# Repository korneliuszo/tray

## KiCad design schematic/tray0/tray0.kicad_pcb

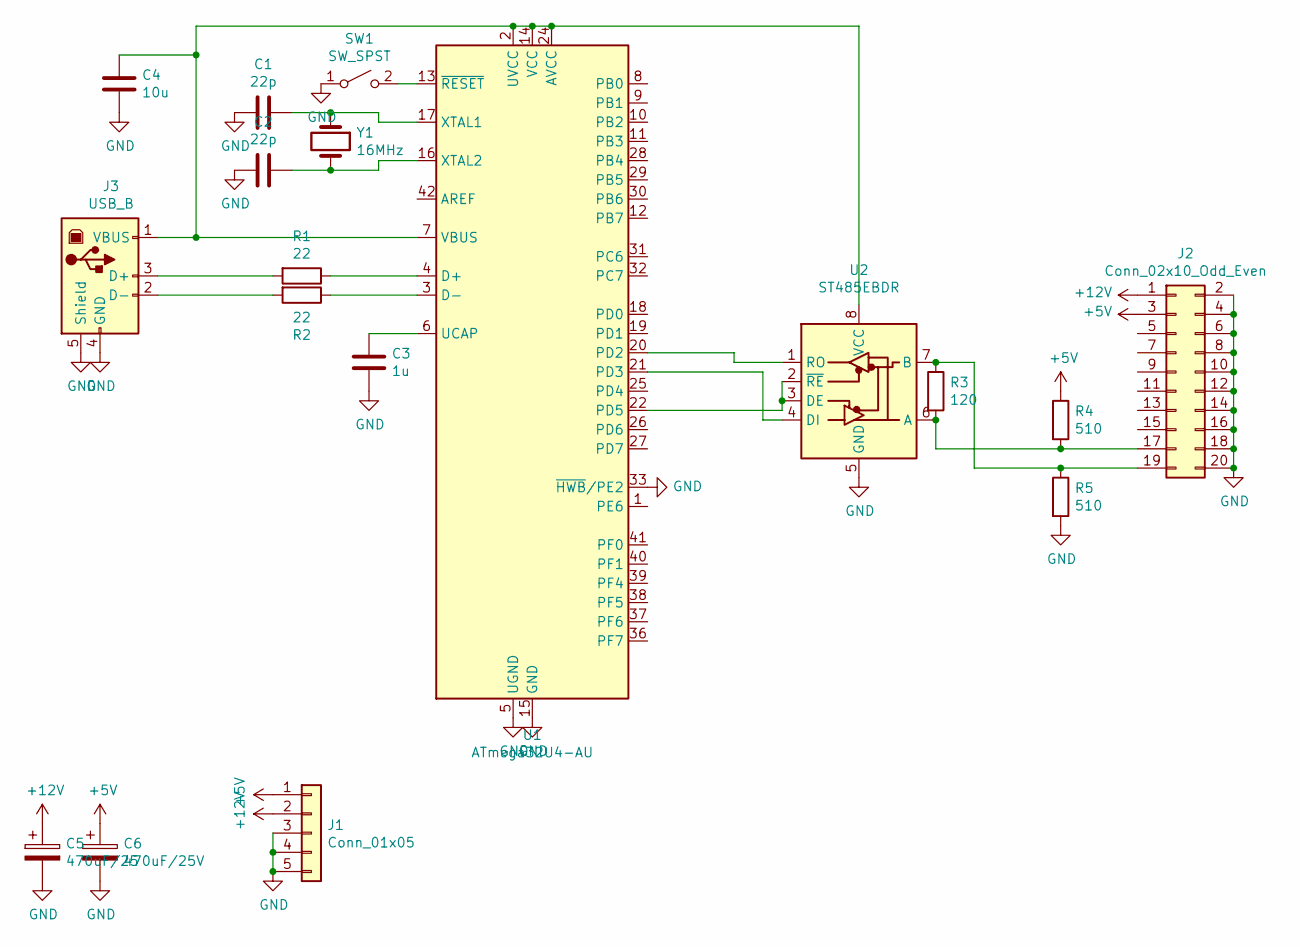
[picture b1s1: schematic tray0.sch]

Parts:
C1, C2: 22p; C_0805_2012Metric
C3: 1u; C_0805_2012Metric
C4: 10u; C_0805_2012Metric
C5: 470uF/25; CP_Radial_D8.0mm_P3.80mm
C6: 470uF/25V; CP_Radial_D8.0mm_P3.80mm
J1: Conn_01x05; PC-MDJ-402-4P
J2: Conn_02x10_Odd_Even; IDC-Header_2x10_P2.54mm_Horizontal
J3: USB_B; USB_B_OST_USB-B1HSxx_Horizontal
R1, R2: 22; R_0805_2012Metric
R3: 120; R_0805_2012Metric
R4, R5: 510; R_0805_2012Metric
SW1: SW_SPST; SW_Tactile_SKHH_Angled
U1: ATmega32U4-AU; TQFP-44_10x10mm_P0.8mm
U2: ST485EBDR; SOIC-8_3.9x4.9mm_P1.27mm
Y1: 16MHz; Crystal_SMD_HC49-SD

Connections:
+5V: C6.1, J1.1, J2.3, R4.1
+12V: C5.1, J1.2, J2.1
GND: C1.2, C2.2, C3.2, C4.2, C5.2, C6.2, J1.3, J1.4, J1.5, J2.2, J2.4, J2.6, J2.8, J2.10, J2.12, J2.14, J2.16, J2.18, J2.20, J3.4 (GND), J3.5 (Shield), R5.2, SW1.1 (A), U1.5 (UGND), U1.15 (GND), U1.23 (GND), U1.33 (~HWB~/PE2), U1.35 (GND), U1.43 (GND), U2.5 (GND)
unnamed: C1.1, U1.17 (XTAL1), Y1.1
unnamed: C2.1, U1.16 (XTAL2), Y1.2
unnamed: C3.1, U1.6 (UCAP)
unnamed: C4.1, J3.1 (VBUS), U1.2 (UVCC), U1.7 (VBUS), U1.14 (VCC), U1.24 (AVCC), U1.34 (VCC), U1.44 (AVCC), U2.8 (VCC)
unnamed: J2.17, R3.2, R4.2, U2.6 (A)
unnamed: J2.19, R3.1, R5.1, U2.7 (B)
unnamed: J3.2 (D-), R2.2
unnamed: J3.3 (D+), R1.2
unnamed: R1.1, U1.4 (D+)
unnamed: R2.1, U1.3 (D-)
unnamed: SW1.2 (B), U1.13 (~RESET)
unnamed: U1.20 (PD2), U2.1 (RO)
unnamed: U1.21 (PD3), U2.4 (DI)
unnamed: U1.22 (PD5), U2.2 (~RE), U2.3 (DE)

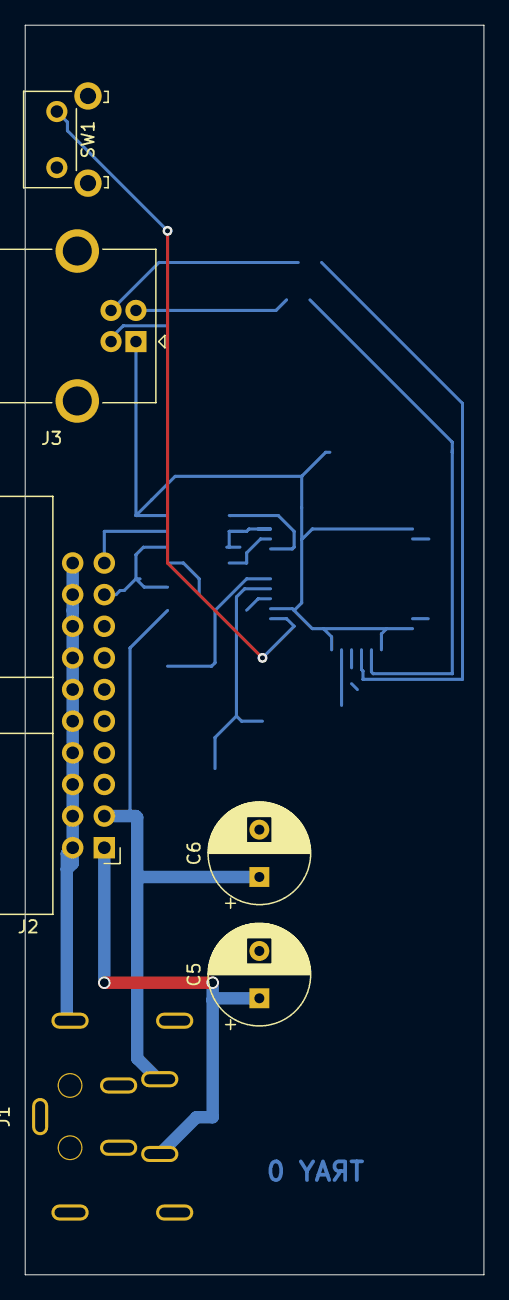
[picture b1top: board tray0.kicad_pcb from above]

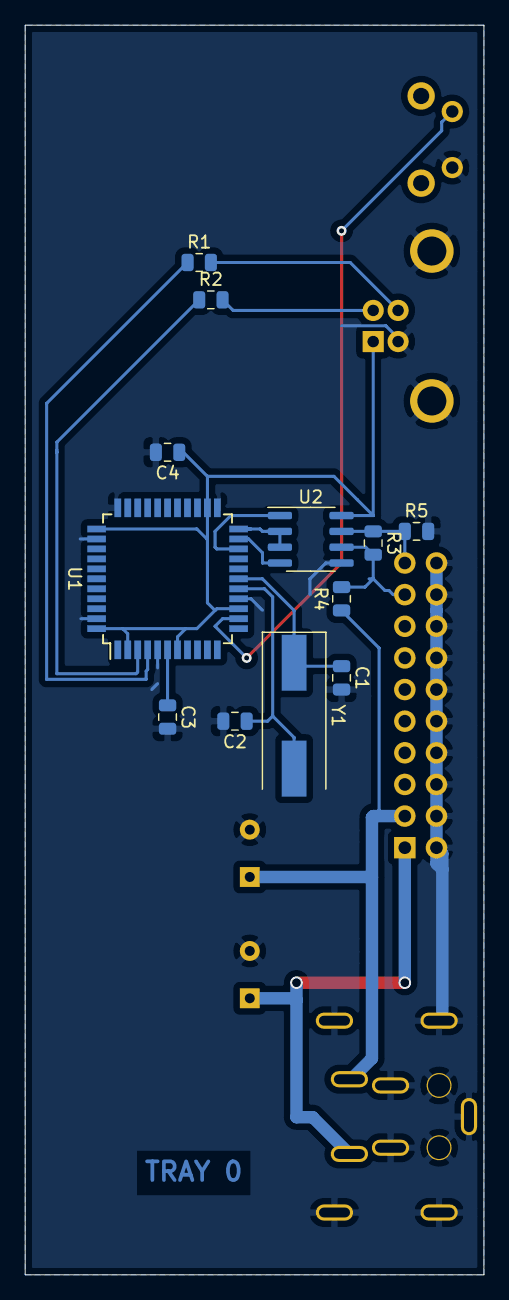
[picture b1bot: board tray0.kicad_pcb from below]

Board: 2 copper layers, 36.8 x 100.3 mm, 18 parts (12 on the bottom side), 17 nets.

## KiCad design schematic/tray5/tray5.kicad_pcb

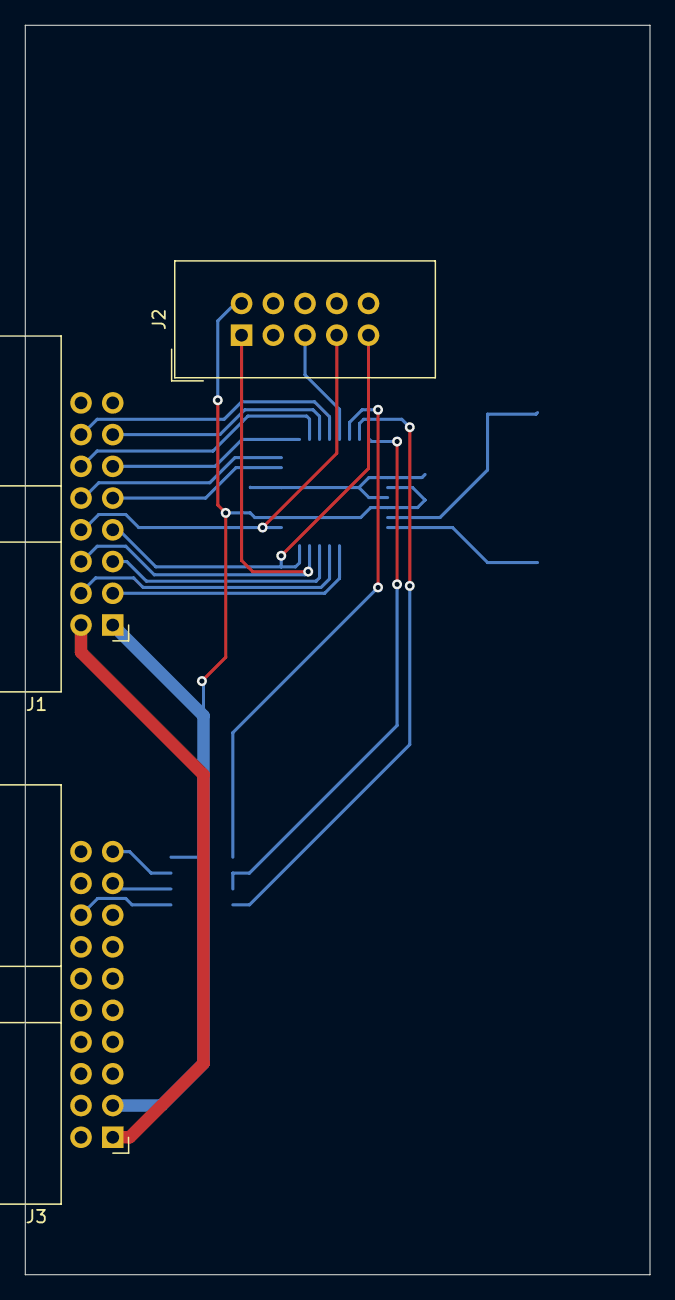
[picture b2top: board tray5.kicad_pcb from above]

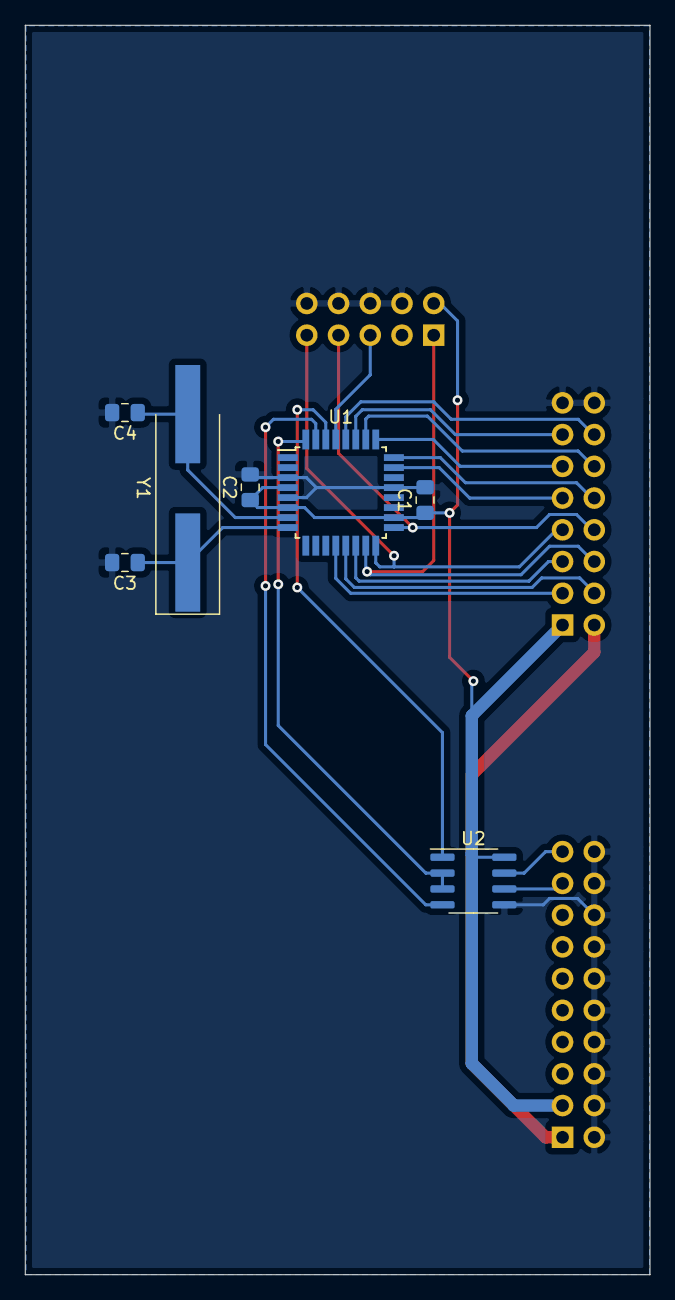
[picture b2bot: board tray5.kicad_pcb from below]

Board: 2 copper layers, 50.0 x 100.0 mm, 10 parts (7 on the bottom side), 23 nets.

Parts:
C1, C2: 100nF; C_0805_2012Metric_Pad1.15x1.40mm_HandSolder
C3, C4: 27p; C_0805_2012Metric_Pad1.15x1.40mm_HandSolder
J1: Conn_02x08_Odd_Even; IDC-Header_2x08_P2.54mm_Horizontal
J2: AVR-ISP-10; IDC-Header_2x05_P2.54mm_Vertical
J3: Conn_02x10_Odd_Even; IDC-Header_2x10_P2.54mm_Horizontal
U1: ATmega328P-AU; TQFP-32_7x7mm_P0.8mm
U2: ST485EBDR; SOIC-8_3.9x4.9mm_P1.27mm
Y1: 16MHz; Crystal_SMD_HC49-SD_HandSoldering

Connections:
GND: C1.2, C2.2, C3.2, C4.2, J1.15, J1.16, J2.4, J2.6, J2.8, J2.10, J3.2, J3.4, J3.6, J3.8, J3.10, J3.12, J3.14, J3.16, J3.18, J3.20, U1.3, U1.5, U1.21, U2.5
unnamed: C3.1, U1.8, Y1.1
unnamed: C4.1, U1.7, Y1.2
unnamed: J1.2, J3.1
unnamed: J2.5, U1.29
unnamed: J3.17, U2.6
unnamed: J3.19, U2.7
unnamed: U1.30, U2.1
unnamed: U1.31, U2.4
unnamed: U1.32, U2.2, U2.3
PB0: J1.3, U1.12
PB1: J1.4, U1.13
PB2: J1.5, U1.14
PB3: J1.6, J2.1, U1.15
PB4: J1.7, J2.9, U1.16
PB5: J1.8, J2.7, U1.17
PC0: J1.9, U1.23
PC1: J1.10, U1.24
PC2: J1.11, U1.25
PC3: J1.12, U1.26
PC4: J1.13, U1.27
PC5: J1.14, U1.28
VCC: C1.1, C2.1, J1.1, J2.2, J3.3, U1.4, U1.6, U1.18, U2.8

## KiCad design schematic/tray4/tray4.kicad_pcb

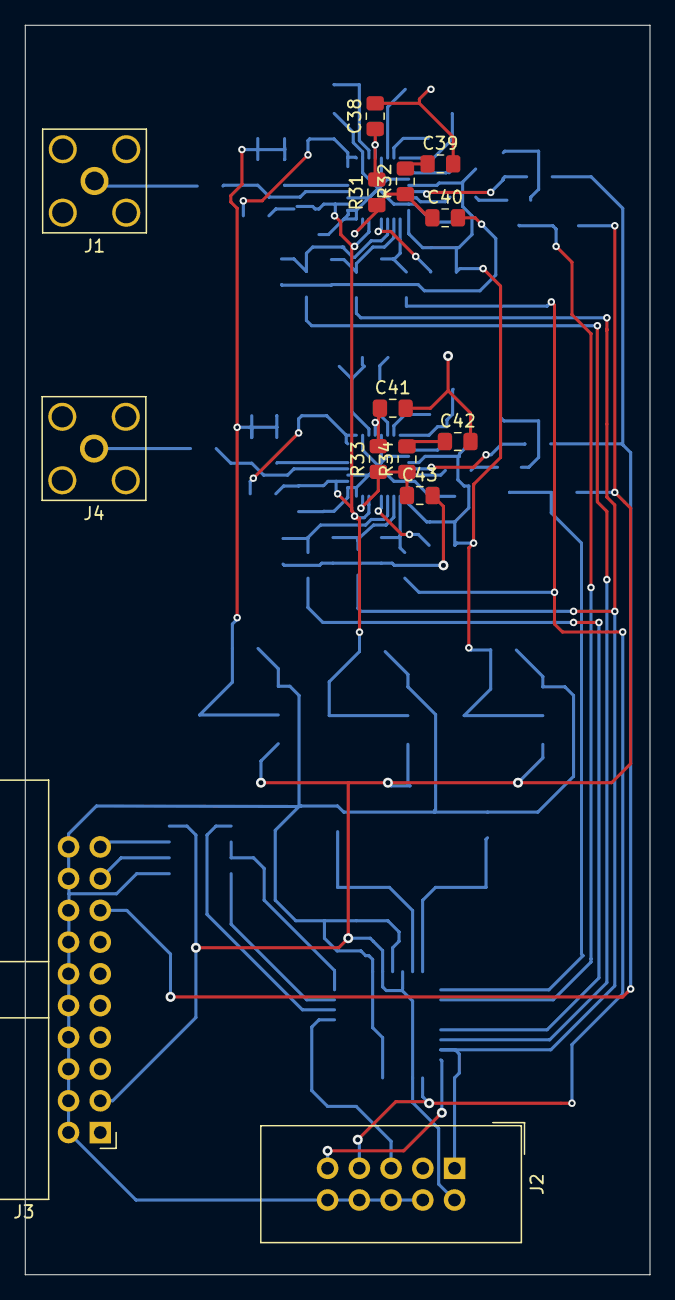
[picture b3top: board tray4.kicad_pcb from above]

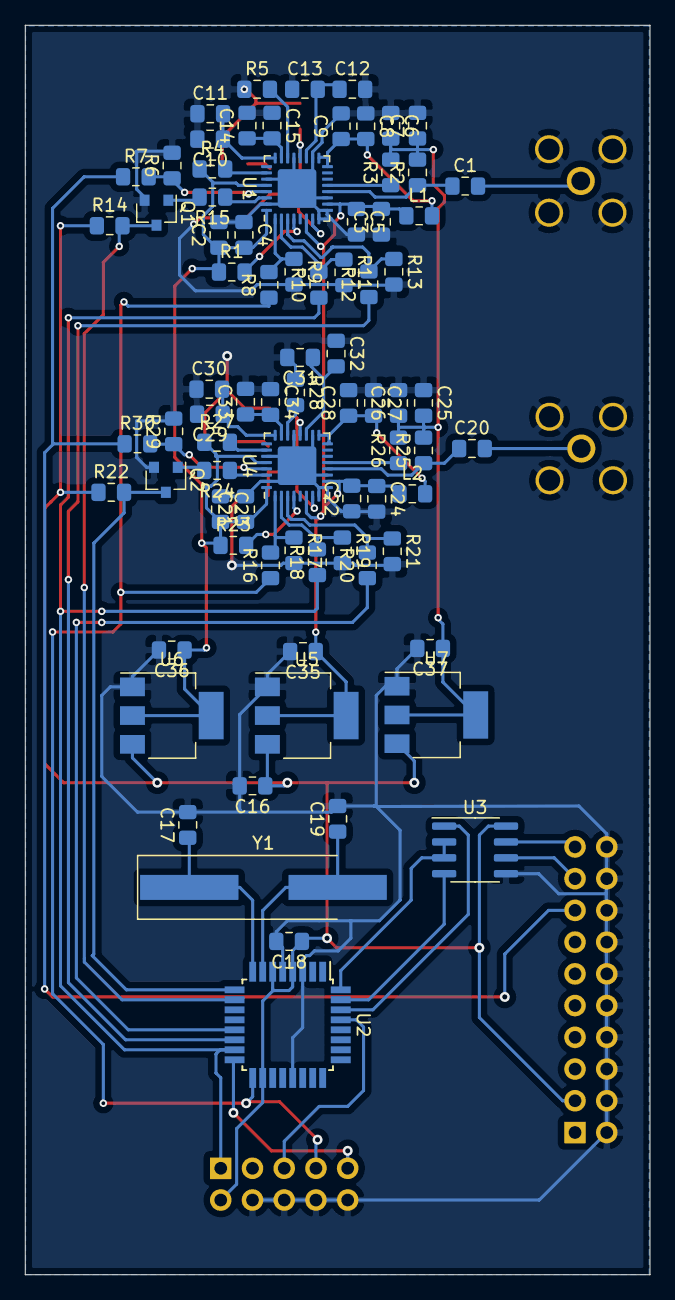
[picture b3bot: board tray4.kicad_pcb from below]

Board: 2 copper layers, 50.0 x 100.0 mm, 93 parts (79 on the bottom side), 59 nets.

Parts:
C1, C20: 100p; C_0805_2012Metric_Pad1.15x1.40mm_HandSolder
C2, C5, C7, C9, C10, C12, C14, C21, C24, C26, C28, C29, C31, C33: 10p; C_0805_2012Metric_Pad1.15x1.40mm_HandSolder
C3, C4, C6, C8, C11, C13, C15, C22, C23, C25, C27, C30, C32, C34, C35, C36, C37: 100n; C_0805_2012Metric_Pad1.15x1.40mm_HandSolder
C16, C18: 100nF; C_0805_2012Metric_Pad1.15x1.40mm_HandSolder
C17, C19: 27p; C_0805_2012Metric_Pad1.15x1.40mm_HandSolder
C38, C41: 10n; C_0805_2012Metric_Pad1.15x1.40mm_HandSolder
C39, C42: 330n; C_0805_2012Metric_Pad1.15x1.40mm_HandSolder
C40, C43: 22n; C_0805_2012Metric_Pad1.15x1.40mm_HandSolder
J1, J4: Conn_Coaxial; SMA_Amphenol_132203-12_Horizontal
J2: AVR-ISP-10; IDC-Header_2x05_P2.54mm_Vertical
J3: Conn_02x10_Odd_Even; IDC-Header_2x10_P2.54mm_Horizontal
L1, L2: 47n; L_0805_2012Metric_Pad1.15x1.40mm_HandSolder
Q1, Q2: BC847; SOT-23
R1, R4, R23, R27: 10k; R_0805_2012Metric_Pad1.15x1.40mm_HandSolder
R2, R3, R25, R26: 50; R_0805_2012Metric_Pad1.15x1.40mm_HandSolder
R5, R28: 4k7; R_0805_2012Metric_Pad1.15x1.40mm_HandSolder
R6, R9, R11, R13, R17, R19, R21, R29: 3k3; R_0805_2012Metric_Pad1.15x1.40mm_HandSolder
R7, R30: 1k8; R_0805_2012Metric_Pad1.15x1.40mm_HandSolder
R8, R10, R12, R16, R18, R20: 2k2; R_0805_2012Metric_Pad1.15x1.40mm_HandSolder
R14, R15, R22, R24: 1k; R_0805_2012Metric_Pad1.15x1.40mm_HandSolder
R31, R33: 180; R_0805_2012Metric_Pad1.15x1.40mm_HandSolder
R32, R34: 82; R_0805_2012Metric_Pad1.15x1.40mm_HandSolder
U1, U4: ADF4351; QFN-32-1EP_5x5mm_P0.5mm_EP3.1x3.1mm
U2: ATmega328P-AU; TQFP-32_7x7mm_P0.8mm
U3: ST485EBDR; SOIC-8_3.9x4.9mm_P1.27mm
U5, U6, U7: AMS1117-3.3; SOT-223-3_TabPin2
Y1: 16MHz; Crystal_SMD_HC49-SD_HandSoldering

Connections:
10MHz: J3.15, R7.1, R30.1
+3.3VA: C3.2, C5.1, C22.2, C24.1, C35.1, L1.1, L2.1, U1.6, U1.10, U4.6, U4.10, U5.2
+3.3VP: C6.2, C7.1, C25.2, C26.1, C37.1, R2.2, R3.2, R25.2, R26.2, U7.2
+3V3: C2.1, C4.2, C21.1, C23.2, C36.1, R1.1, R4.1, R23.1, R27.1, U1.28, U1.32, U4.28, U4.32, U6.2
CP0: C40.1, R31.1, R32.1, U1.7
CP1: C43.1, R33.1, R34.1, U4.7
GND: C2.2, C3.1, C4.1, C5.2, C6.1, C7.2, C8.1, C9.2, C10.2, C11.1, C12.2, C13.1, C14.2, C15.1, C16.2, C17.2, C18.2, C19.2, C21.2, C22.1, C23.1, C24.2, C25.1, C26.2, C27.1, C28.2, C29.2, C30.1, C31.2, C32.1, C33.2, C34.1, C35.2, C36.2, C37.2, C38.2, C39.2, C40.2, C41.2, C42.2, C43.2, J1.2, J2.4, J2.6, J2.8, J2.10, J3.2, J3.4, J3.6, J3.8, J3.10, J3.12, J3.14, J3.16, J3.18, J3.20, J4.2, Q1.2, Q2.2, R5.1, R6.2, R9.2, R11.2, R13.2, R17.2, R19.2, R21.2, R28.1, R29.2, U1.8, U1.9, U1.11, U1.18, U1.21, U1.27, U1.31, U1.33, U2.3, U2.5, U2.21, U3.5, U4.8, U4.9, U4.11, U4.18, U4.21, U4.27, U4.31, U4.33, U5.1, U6.1, U7.1
LE0: R12.1, U2.14
LE1: R20.1, U2.13
MOSI: J2.1, R10.1, R18.1, U2.15
MUXOUT0: Q1.3, R14.2, U2.10
MUXOUT1: Q2.3, R22.2, U2.9
unnamed: C1.1, R2.1, U1.12
unnamed: C1.2, J1.1
unnamed: C8.2, C9.1, L1.2, U1.16, U1.17
unnamed: C10.1, C11.2, U1.24
unnamed: C12.1, C13.2, U1.19
unnamed: C14.1, C15.2, U1.23
unnamed: C17.1, U2.8, Y1.1
unnamed: C19.1, U2.7, Y1.2
unnamed: C20.1, R25.1, U4.12
unnamed: C20.2, J4.1
unnamed: C27.2, C28.1, L2.2, U4.16, U4.17
unnamed: C29.1, C30.2, U4.24
unnamed: C31.1, C32.2, U4.19
unnamed: C33.1, C34.2, U4.23
unnamed: C38.1, R31.2, U1.20
unnamed: C39.1, R32.2
unnamed: C41.1, R33.2, U4.20
unnamed: C42.1, R34.2
unnamed: J2.5, U2.29
unnamed: J2.9, U2.16
unnamed: J3.17, U3.6
unnamed: J3.19, U3.7
unnamed: Q1.1, R15.2
unnamed: Q2.1, R24.2
unnamed: R1.2, U1.4
unnamed: R3.1, U1.13
unnamed: R4.2, U1.26
unnamed: R5.2, U1.22
unnamed: R6.1, R7.2, U1.29
unnamed: R8.2, R9.1, U1.1
unnamed: R10.2, R11.1, U1.2
unnamed: R12.2, R13.1, U1.3
unnamed: R15.1, U1.30
unnamed: R16.2, R17.1, U4.1
unnamed: R18.2, R19.1, U4.2
unnamed: R20.2, R21.1, U4.3
unnamed: R23.2, U4.4
unnamed: R24.1, U4.30
unnamed: R26.1, U4.13
unnamed: R27.2, U4.26
unnamed: R28.2, U4.22
unnamed: R29.1, R30.2, U4.29
unnamed: U2.30, U3.1
unnamed: U2.31, U3.4
unnamed: U2.32, U3.2, U3.3
SCK: J2.7, R8.1, R16.1, U2.17
VCC: C16.1, C18.1, J2.2, J3.3, R14.1, R22.1, U2.4, U2.6, U2.18, U3.8, U5.3, U6.3, U7.3

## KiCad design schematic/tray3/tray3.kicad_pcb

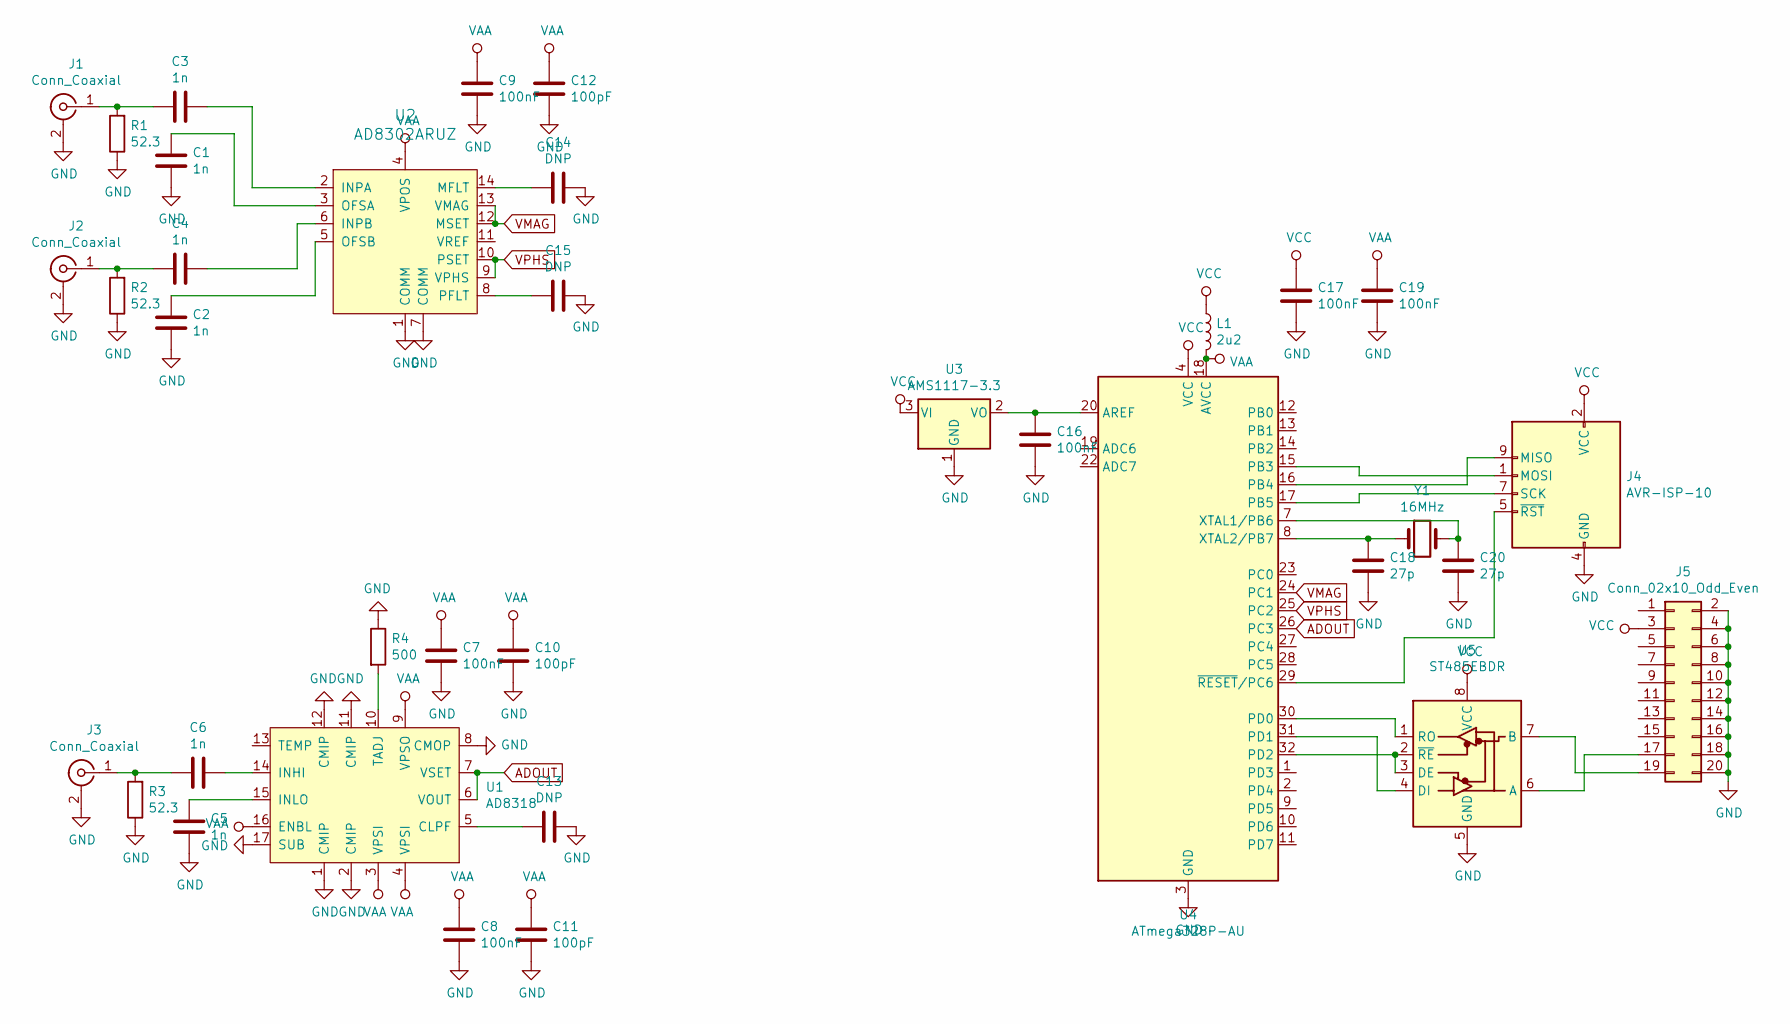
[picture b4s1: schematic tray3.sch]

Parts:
C1, C2, C3, C4, C5, C6: 1n; C_0805_2012Metric_Pad1.15x1.40mm_HandSolder
C7, C8, C9, C16, C17, C19: 100nF; C_0805_2012Metric_Pad1.15x1.40mm_HandSolder
C10, C11, C12: 100pF; C_0805_2012Metric_Pad1.15x1.40mm_HandSolder
C13, C14, C15: DNP; C_0805_2012Metric_Pad1.15x1.40mm_HandSolder
C18, C20: 27p; C_0805_2012Metric_Pad1.15x1.40mm_HandSolder
J1, J2, J3: Conn_Coaxial; SMA_Molex_73251-2200_Horizontal
J4: AVR-ISP-10; IDC-Header_2x05_P2.54mm_Vertical
J5: Conn_02x10_Odd_Even; IDC-Header_2x10_P2.54mm_Horizontal
L1: 2u2; L_1210_3225Metric_Pad1.42x2.65mm_HandSolder
R1, R2, R3: 52.3; R_1206_3216Metric_Pad1.42x1.75mm_HandSolder
R4: 500; R_0805_2012Metric_Pad1.15x1.40mm_HandSolder
U1: AD8318; QFN-16-1EP_4x4mm_P0.65mm_EP2.5x2.5mm
U2: AD8302ARUZ; TSSOP-14_4.4x5mm_P0.65mm; MPN AD8302ARUZ; Digi-Key_PN AD8302ARUZ-ND
U3: AMS1117-3.3; SOT-223-3_TabPin2
U4: ATmega328P-AU; TQFP-32_7x7mm_P0.8mm
U5: ST485EBDR; SOIC-8_3.9x4.9mm_P1.27mm
Y1: 16MHz; Crystal_SMD_HC49-SD_HandSoldering

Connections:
ADOUT: U1.6 (VOUT), U1.7 (VSET), U4.26 (PC3)
GND: C1.2, C2.2, C5.2, C7.2, C8.2, C9.2, C10.2, C11.2, C12.2, C13.1, C14.1, C15.1, C16.2, C17.2, C18.2, C19.2, C20.2, J1.2 (Ext), J2.2 (Ext), J3.2 (Ext), J4.4 (GND), J4.6 (GND), J4.8 (GND), J4.10 (GND), J5.2, J5.4, J5.6, J5.8, J5.10, J5.12, J5.14, J5.16, J5.18, J5.20, R1.1, R2.1, R3.1, R4.1, U1.1 (CMIP), U1.2 (CMIP), U1.8 (CMOP), U1.11 (CMIP), U1.12 (CMIP), U1.17 (SUB), U2.1 (COMM), U2.7 (COMM), U3.1 (GND), U4.3 (GND), U4.5 (GND), U4.21 (GND), U5.5 (GND)
unnamed: C1.1, U2.3 (OFSA)
unnamed: C2.1, U2.5 (OFSB)
unnamed: C3.1, U2.2 (INPA)
unnamed: C3.2, J1.1 (In), R1.2
unnamed: C4.1, U2.6 (INPB)
unnamed: C4.2, J2.1 (In), R2.2
unnamed: C5.1, U1.15 (INLO)
unnamed: C6.1, U1.14 (INHI)
unnamed: C6.2, J3.1 (In), R3.2
unnamed: C13.2, U1.5 (CLPF)
unnamed: C14.2, U2.14 (MFLT)
unnamed: C15.2, U2.8 (PFLT)
unnamed: C16.1, U3.2 (VO), U4.20 (AREF)
unnamed: C18.1, U4.8 (XTAL2/PB7), Y1.1
unnamed: C20.1, U4.7 (XTAL1/PB6), Y1.2
unnamed: J4.1 (MOSI), U4.15 (PB3)
unnamed: J4.5 (~RST), U4.29 (~RESET~/PC6)
unnamed: J4.7 (SCK), U4.17 (PB5)
unnamed: J4.9 (MISO), U4.16 (PB4)
unnamed: J5.17, U5.6 (A)
unnamed: J5.19, U5.7 (B)
unnamed: R4.2, U1.10 (TADJ)
unnamed: U4.30 (PD0), U5.1 (RO)
unnamed: U4.31 (PD1), U5.4 (DI)
unnamed: U4.32 (PD2), U5.2 (~RE), U5.3 (DE)
VAA: C7.1, C8.1, C9.1, C10.1, C11.1, C12.1, C19.1, L1.2, U1.3 (VPSI), U1.4 (VPSI), U1.9 (VPSO), U1.16 (ENBL), U2.4 (VPOS), U4.18 (AVCC)
VCC: C17.1, J4.2 (VCC), J5.3, L1.1, U3.3 (VI), U4.4 (VCC), U4.6 (VCC), U5.8 (VCC)
VMAG: U2.12 (MSET), U2.13 (VMAG), U4.24 (PC1)
VPHS: U2.9 (VPHS), U2.10 (PSET), U4.25 (PC2)

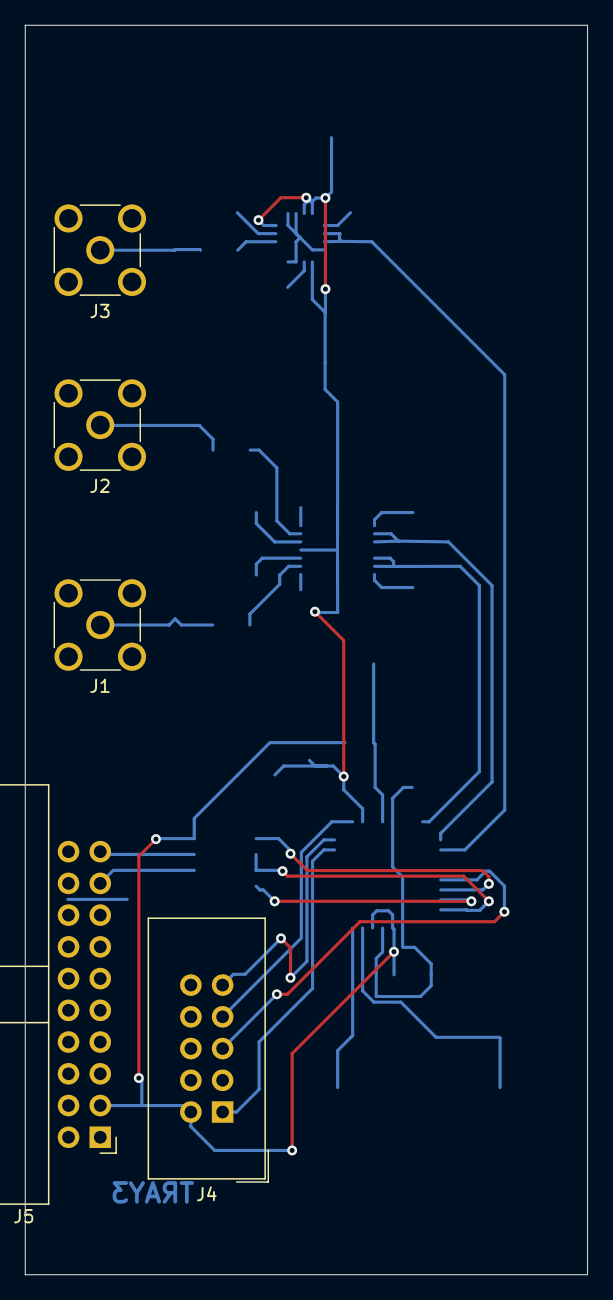
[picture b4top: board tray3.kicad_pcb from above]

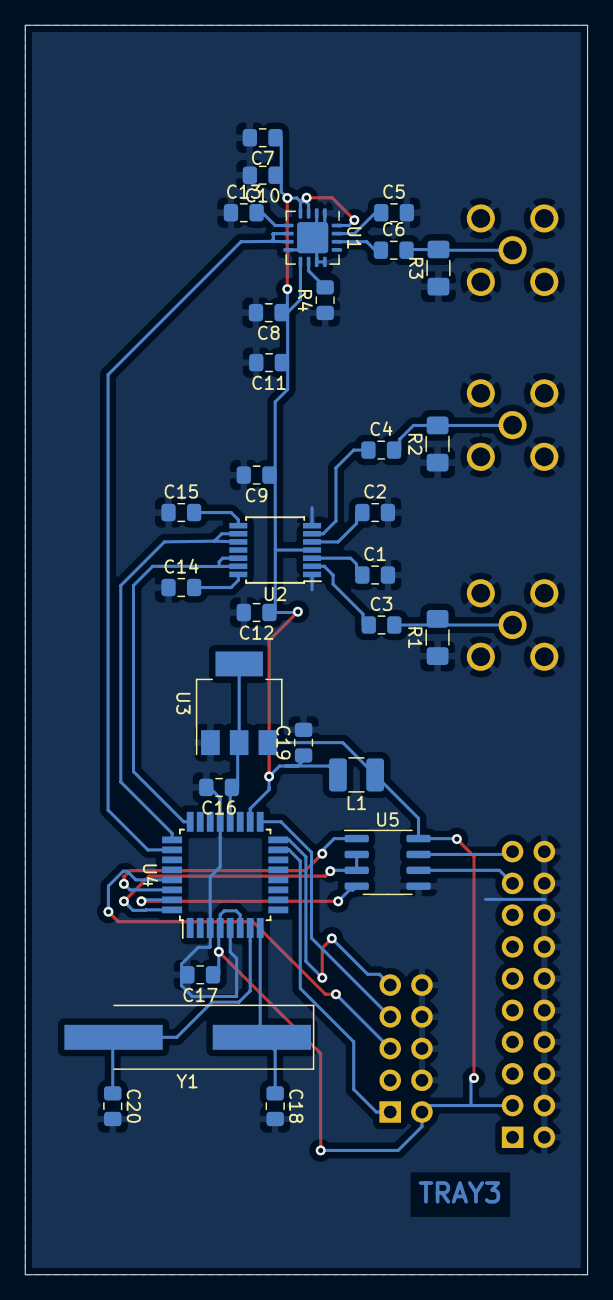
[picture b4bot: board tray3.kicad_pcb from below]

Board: 2 copper layers, 45.0 x 100.0 mm, 36 parts (31 on the bottom side), 31 nets.

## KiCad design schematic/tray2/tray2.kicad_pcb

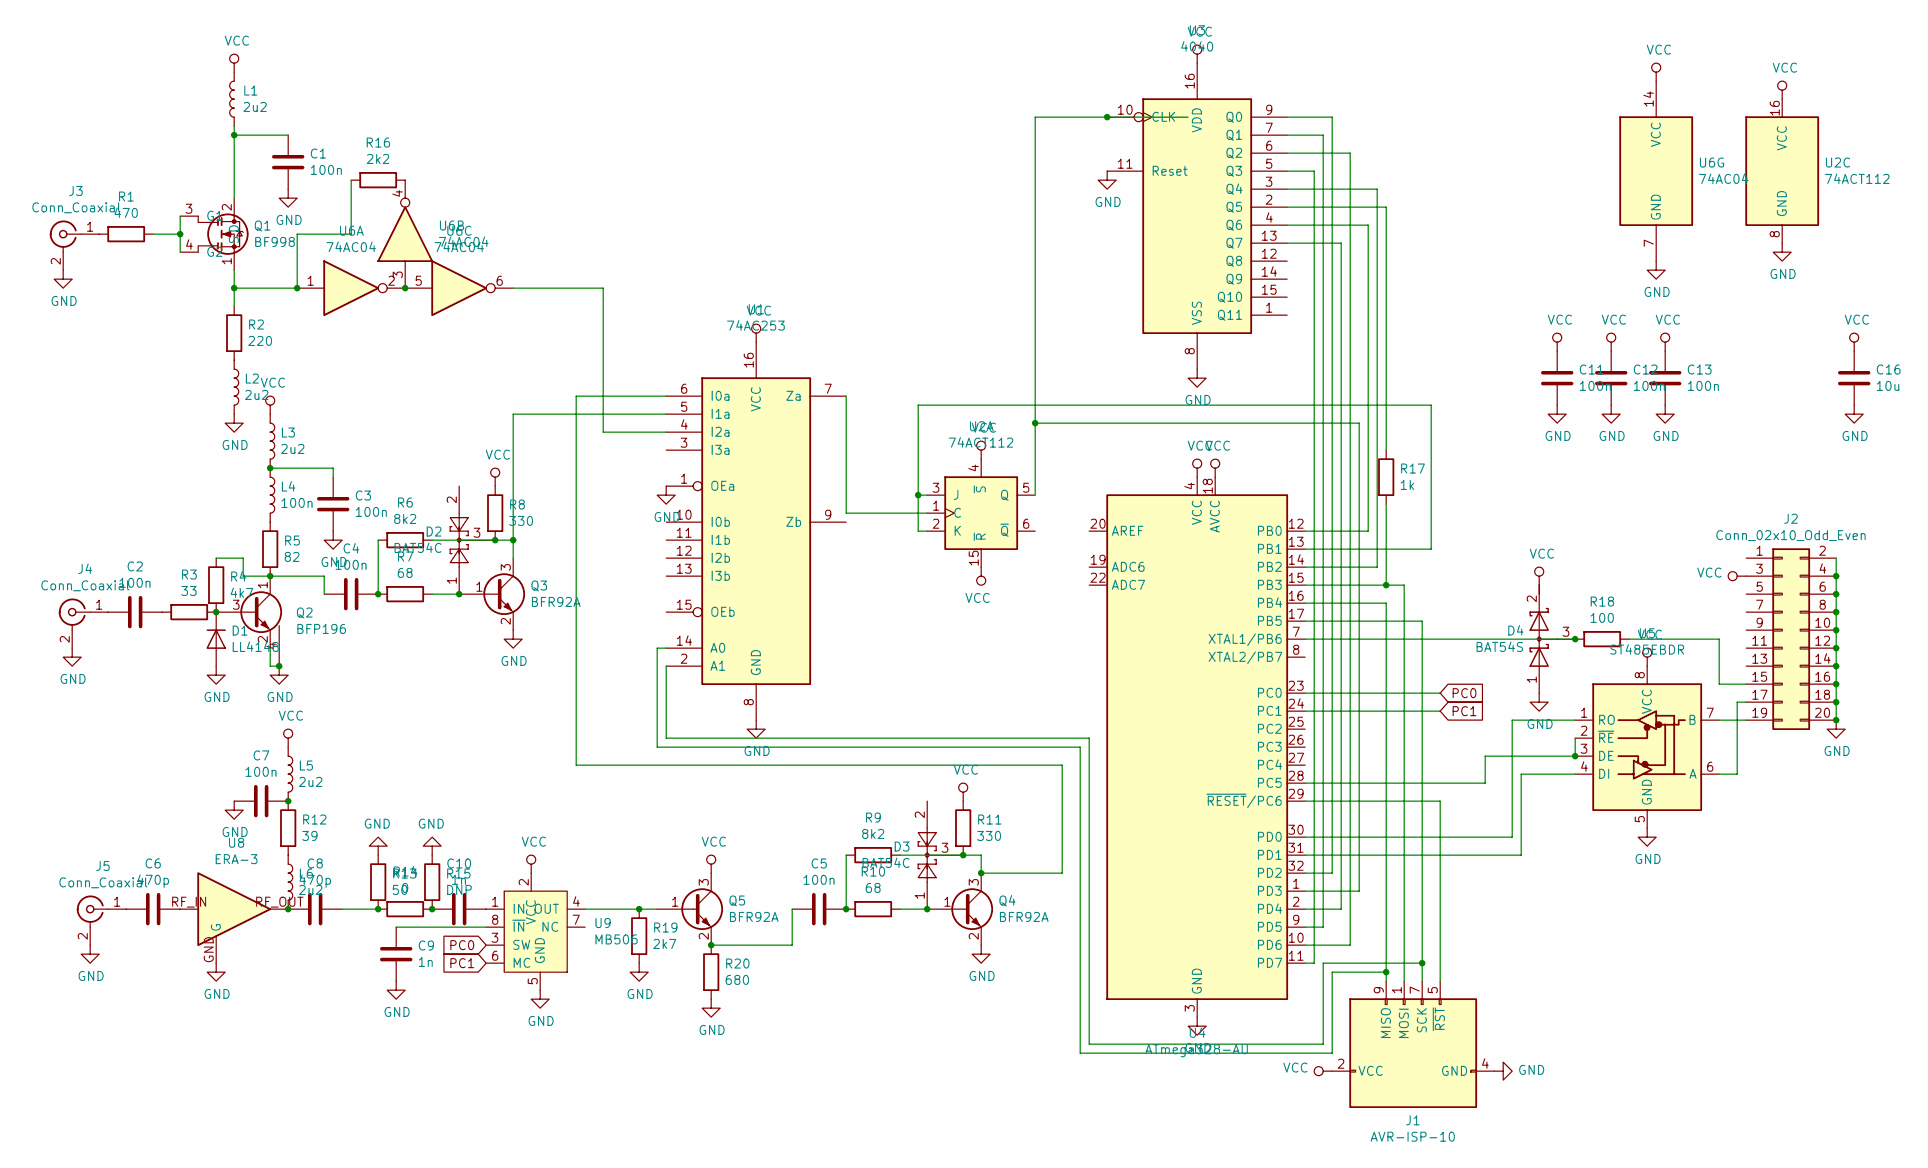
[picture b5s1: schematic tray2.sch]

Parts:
C1, C2, C3, C4, C5, C7, C11, C12, C13: 100n; C_0805_2012Metric
C6, C8: 470p; C_0805_2012Metric
C9, C10: 1n; C_0805_2012Metric
C16: 10u; C_0805_2012Metric
D1: LL4148; D_MiniMELF
D2, D3: BAT54C; SOT-23
D4: BAT54S; SOT-23
J1: AVR-ISP-10; IDC-Header_2x05_P2.54mm_Vertical
J2: Conn_02x10_Odd_Even; IDC-Header_2x10_P2.54mm_Horizontal
J3, J4: Conn_Coaxial; BNC_Amphenol_B6252HB-NPP3G-50_Horizontal
J5: Conn_Coaxial; SMA_Molex_73251-2200_Horizontal
L1, L2, L3, L5, L6: 2u2; L_1210_3225Metric
L4: 100n; L_0805_2012Metric
Q1: BF998; SOT-143
Q2: BFP196; SOT-143
Q3, Q4, Q5: BFR92A; SOT-23
R1: 470; R_0805_2012Metric
R2: 220; R_0805_2012Metric
R3: 33; R_0805_2012Metric
R4: 4k7; R_0805_2012Metric
R5: 82; R_0805_2012Metric
R6, R9: 8k2; R_0805_2012Metric
R7, R10: 68; R_0805_2012Metric
R8, R11: 330; R_0805_2012Metric
R12: 39; R_0805_2012Metric
R13: 50; R_0805_2012Metric
R14: 0; R_0805_2012Metric
R15: DNP; R_0805_2012Metric
R16: 2k2; R_0805_2012Metric
R17: 1k; R_0805_2012Metric
R18: 100; R_0805_2012Metric_Pad1.15x1.40mm_HandSolder
R19: 2k7; R_0805_2012Metric_Pad1.15x1.40mm_HandSolder
R20: 680; R_0805_2012Metric_Pad1.15x1.40mm_HandSolder
U1: 74AC253; SOIC-16_3.9x9.9mm_P1.27mm
U2: 74ACT112; SOIC-16_3.9x9.9mm_P1.27mm
U3: 4040; SOIC-16_3.9x9.9mm_P1.27mm
U4: ATmega328-AU; TQFP-32_7x7mm_P0.8mm
U5: ST485EBDR; SOIC-8_3.9x4.9mm_P1.27mm
U6: 74AC04; SOIC-14_3.9x8.7mm_P1.27mm
U8: ERA-3; WW107
U9: MB506; SO-8_5.3x6.2mm_P1.27mm

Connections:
GND: C1.2, C3.2, C7.2, C9.2, C11.2, C12.2, C13.2, C16.2, D1.2 (A), D4.1 (A), J1.4 (GND), J1.6 (GND), J1.8 (GND), J1.10 (GND), J2.2, J2.4, J2.6, J2.8, J2.10, J2.12, J2.14, J2.16, J2.18, J2.20, J3.2 (Ext), J4.2 (Ext), J5.2 (Ext), L2.2, Q2.2 (E), Q2.4, Q3.2 (E), Q4.2 (E), R13.1, R15.1, R19.2, R20.2, U1.1 (OEa), U1.8 (GND), U2.8 (GND), U3.8 (VSS), U3.11 (Reset), U4.3 (GND), U4.5 (GND), U4.21 (GND), U5.5 (GND), U6.7 (GND), U8.GND (G), U9.5 (GND)
unnamed: C1.1, L1.1, Q1.2 (D)
unnamed: C2.1, R3.2
unnamed: C2.2, J4.1 (In)
unnamed: C3.1, L3.2, L4.1
unnamed: C4.1, R6.2, R7.2
unnamed: C4.2, Q2.1 (C), R4.1, R5.2
unnamed: C5.1, R9.2, R10.2
unnamed: C5.2, Q5.2 (E), R20.1
unnamed: C6.1, U8.RF_IN
unnamed: C6.2, J5.1 (In)
unnamed: C7.1, L5.2, R12.1
unnamed: C8.1, R13.2, R14.2
unnamed: C8.2, L6.2, U8.RF_OUT
unnamed: C9.1, U9.8 (~IN)
unnamed: C10.1, U9.1 (IN)
unnamed: C10.2, R14.1, R15.2
unnamed: D1.1 (K), Q2.3 (B), R3.1, R4.2
unnamed: D2.1, Q3.1 (B), R7.1
unnamed: D2.3, Q3.3 (C), R6.1, R8.2, U1.5 (I1a)
unnamed: D3.1, Q4.1 (B), R10.1
unnamed: D3.3, Q4.3 (C), R9.1, R11.2, U1.6 (I0a)
unnamed: D4.3 (common), R18.2, U4.7 (XTAL1/PB6)
unnamed: J1.1 (MOSI), R17.2, U4.15 (PB3)
unnamed: J1.5 (~RST), U4.29 (~RESET~/PC6)
unnamed: J1.7 (SCK), U1.2 (A1), U4.17 (PB5)
unnamed: J1.9 (MISO), U1.14 (A0), U4.16 (PB4)
unnamed: J2.15, R18.1
unnamed: J2.17, U5.6 (A)
unnamed: J2.19, U5.7 (B)
unnamed: J3.1 (In), R1.2
unnamed: L2.1, R2.2
unnamed: L4.2, R5.1
unnamed: L6.1, R12.2
unnamed: Q1.1 (S), R2.1, R16.2, U6.1
unnamed: Q1.3 (G1), Q1.4 (G2), R1.1
unnamed: Q5.1 (B), R19.1, U9.4 (OUT)
unnamed: R16.1, U6.4
unnamed: R17.1, U3.2 (Q5)
unnamed: U1.4 (I2a), U6.6
unnamed: U1.7 (Za), U2.1 (C)
unnamed: U2.2 (K), U2.3 (J), U4.13 (PB1)
unnamed: U2.5 (Q), U3.10 (CLK), U4.1 (PD3)
unnamed: U3.3 (Q4), U4.14 (PB2)
unnamed: U3.4 (Q6), U4.12 (PB0)
unnamed: U3.5 (Q3), U4.11 (PD7)
unnamed: U3.6 (Q2), U4.10 (PD6)
unnamed: U3.7 (Q1), U4.9 (PD5)
unnamed: U3.9 (Q0), U4.32 (PD2)
unnamed: U3.13 (Q7), U4.2 (PD4)
unnamed: U4.28 (PC5), U5.2 (~RE), U5.3 (DE)
unnamed: U4.30 (PD0), U5.1 (RO)
unnamed: U4.31 (PD1), U5.4 (DI)
unnamed: U6.2, U6.3, U6.5
PC0: U4.23 (PC0), U9.3 (SW)
PC1: U4.24 (PC1), U9.6 (MC)
VCC: C11.1, C12.1, C13.1, C16.1, D4.2 (K), J1.2 (VCC), J2.3, L1.2, L3.1, L5.1, Q5.3 (C), R8.1, R11.1, U1.16 (VCC), U2.4 (~S), U2.15 (~R), U2.16 (VCC), U3.16 (VDD), U4.4 (VCC), U4.6 (VCC), U4.18 (AVCC), U5.8 (VCC), U6.14 (VCC), U9.2 (VCC)

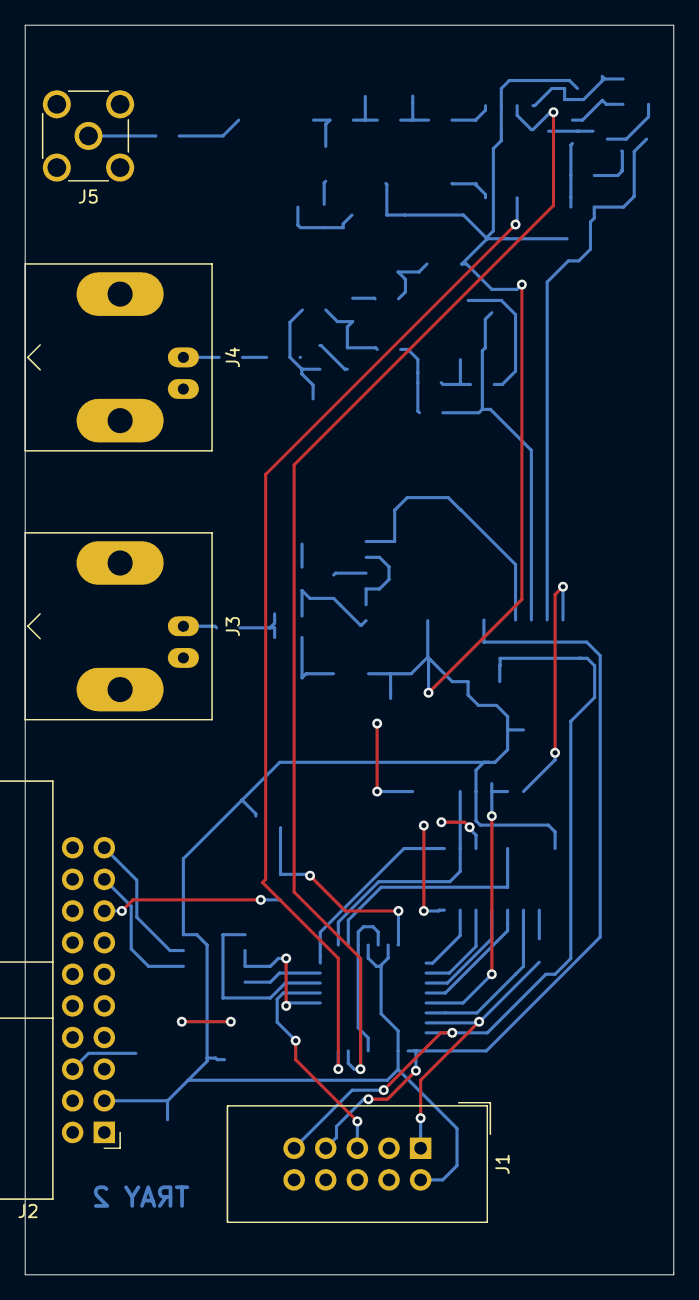
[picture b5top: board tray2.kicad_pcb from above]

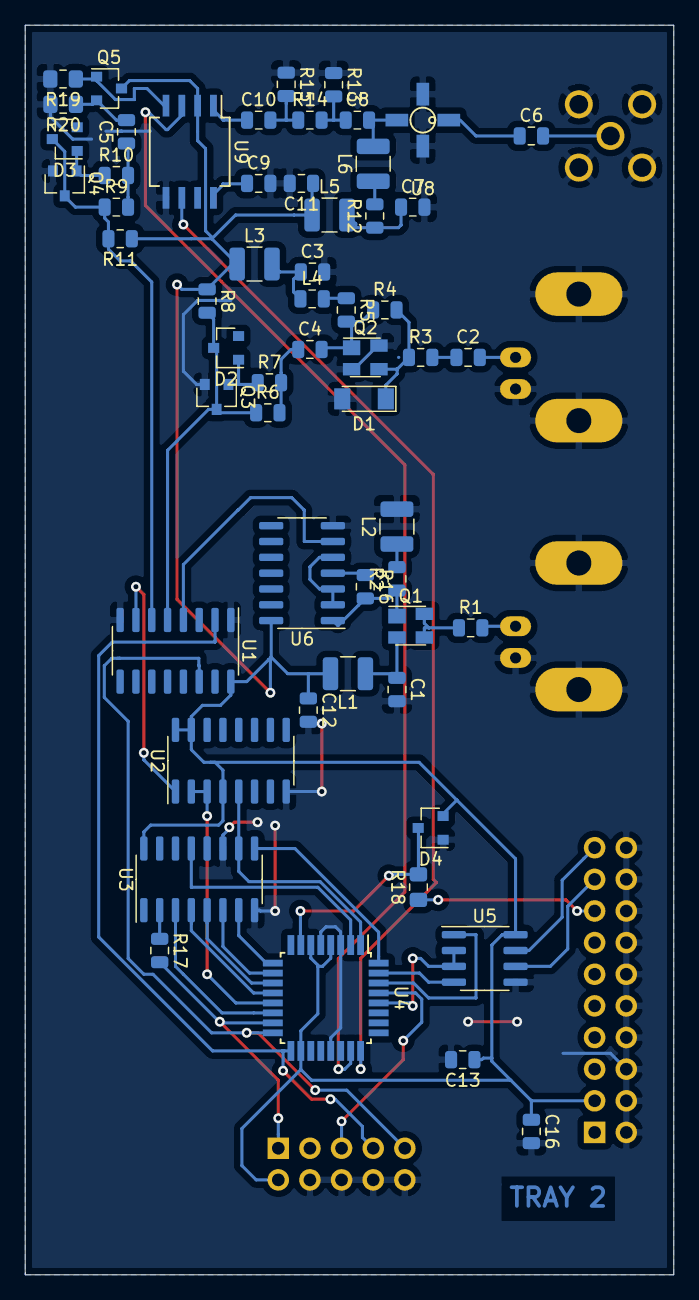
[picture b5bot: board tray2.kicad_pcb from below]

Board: 2 copper layers, 52.1 x 100.3 mm, 62 parts (57 on the bottom side), 57 nets.
